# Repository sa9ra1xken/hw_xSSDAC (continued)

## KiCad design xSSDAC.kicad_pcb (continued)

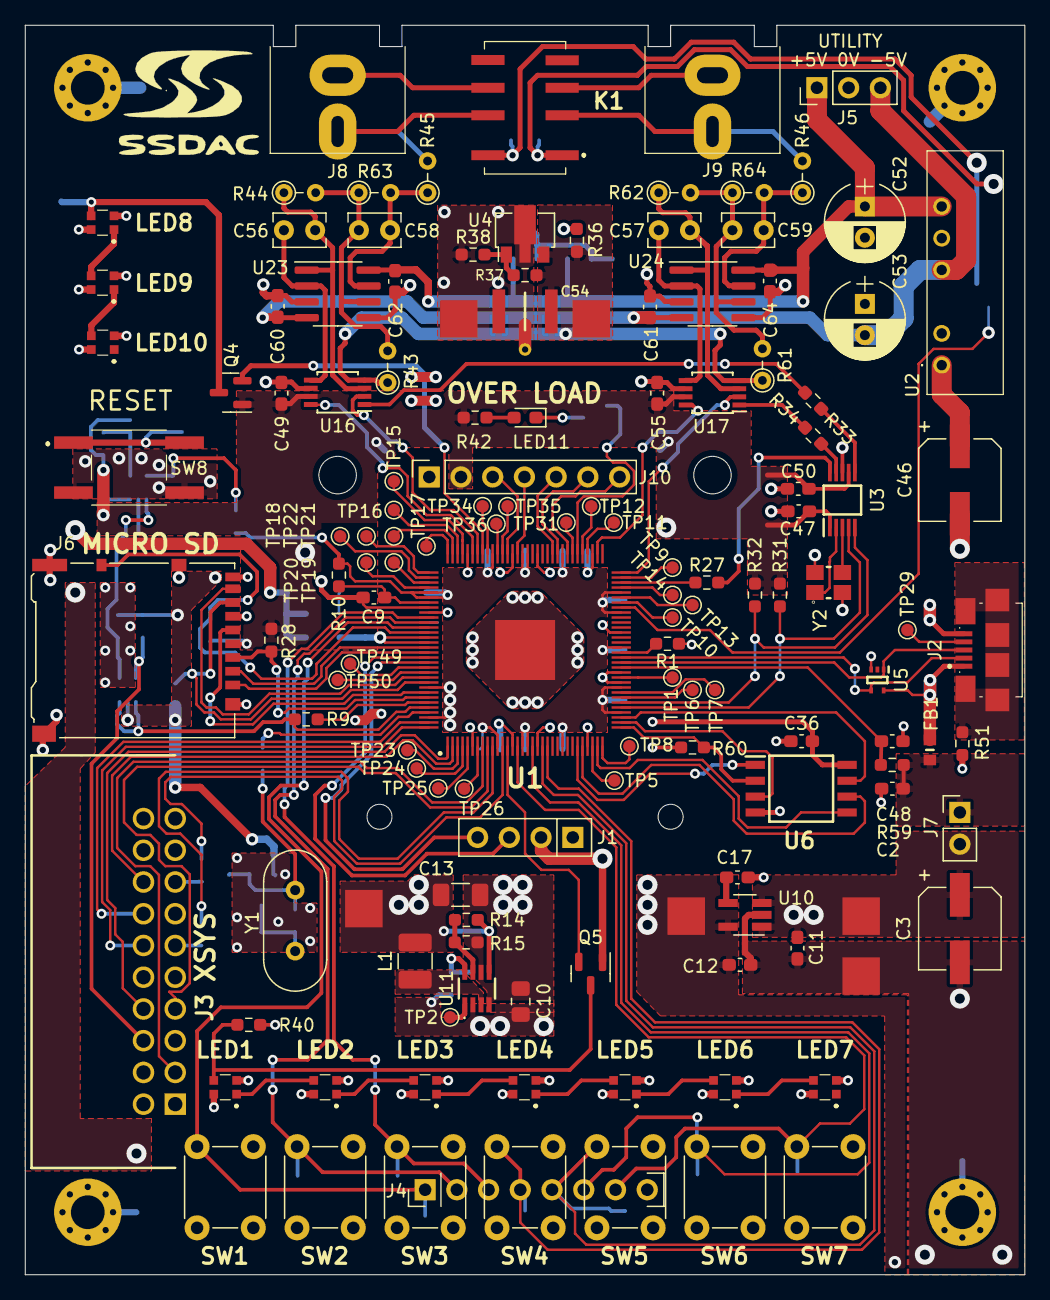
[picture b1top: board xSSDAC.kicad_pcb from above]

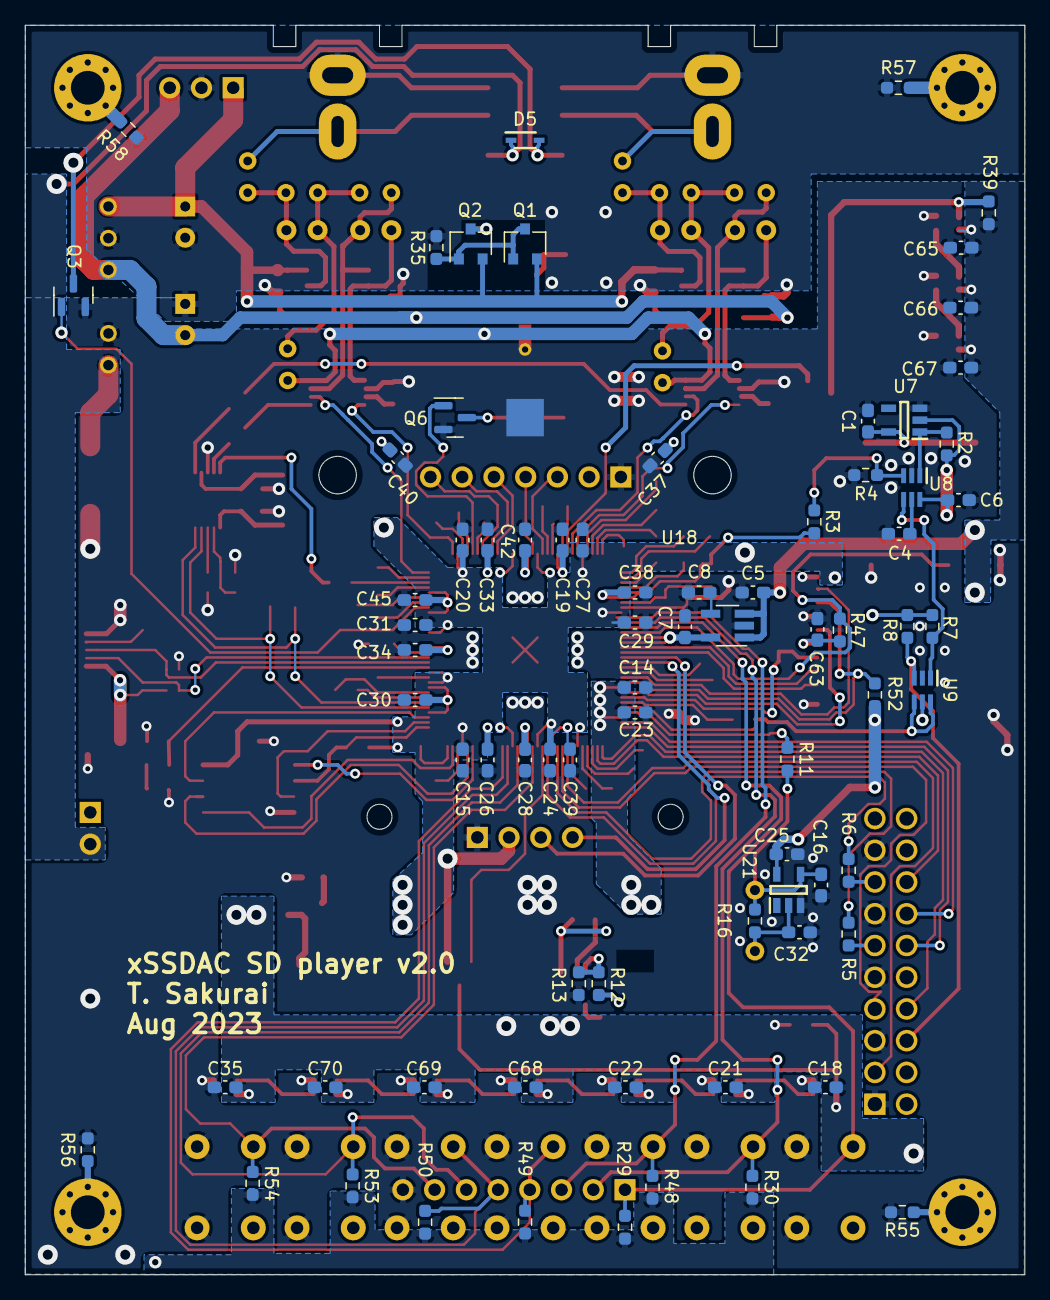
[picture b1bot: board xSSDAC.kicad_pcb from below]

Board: 2 copper layers, 80.0 x 100.0 mm, 221 parts (77 on the bottom side), 149 nets.

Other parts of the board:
C18, C21, C22, C35, C65, C66, C67, C68, C69, C70: 100n; C_0603_1608Metric_Pad1.08x0.95mm_HandSolder
LED11: LED(Red); LED_0603_1608Metric_Pad1.05x0.95mm_HandSolder
Q5: BSS138; SOT-23
R40: 1K; R_0603_1608Metric_Pad0.98x0.95mm_HandSolder
TP2: TestPoint; TestPoint_Pad_D1.0mm_noCrtYd
TP3: TestPoint; TestPoint_Pad_3.0x3.0mm

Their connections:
X1D35: Q5.2 (S); also elsewhere on the board

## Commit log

2024-04-16 V1.0
2024-04-16 V1.1
2024-04-16 V2.0
2024-04-28 removed unudrf folder
2024-04-28 Create README.md
    readme
2024-04-28 Delete xSSDAC_2.0.zip
    redundant zip file
2024-04-28 readme
2024-04-28 port map added
    port map added
2025-10-22 house keep
2025-11-06 3D rendering created.
